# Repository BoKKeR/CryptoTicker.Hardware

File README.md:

# Work in progress

# CryptoTicker.Hardware
CryptoTicker is an information display board that supports over 1500 coin pairs. The PCB consists of 4 individual 1.3" OLED displays controlled by an ESP32. These displays can show a coin pair each. The display outputs are shifted using a multiplexor. Updating or changing the information on the fly is possible from the localhost web server that is running on the device. Vertical and Horizontal positioning is possible. There are 4 programable push-buttons located on the back of the device.
The device can be extendable to support up to 8 displays or with extra multiplexors up to 64 displays.
# Is [coin] supported?
The full list of supported coins can be found at https://coinmarketcap.com/all/views/all/
# Where is the software?
The software is available on the second repository: https://github.com/BoKKeR/CryptoTicker.Software/
# What is missing
There will be an additional board that will be powering the CryptoTicker PCB and serving as the USB to serial converter for the EPS32. There are smaller problems with this design. The files will be updated soon.
# Schematics

# PCB Design

# BOM
Incoming

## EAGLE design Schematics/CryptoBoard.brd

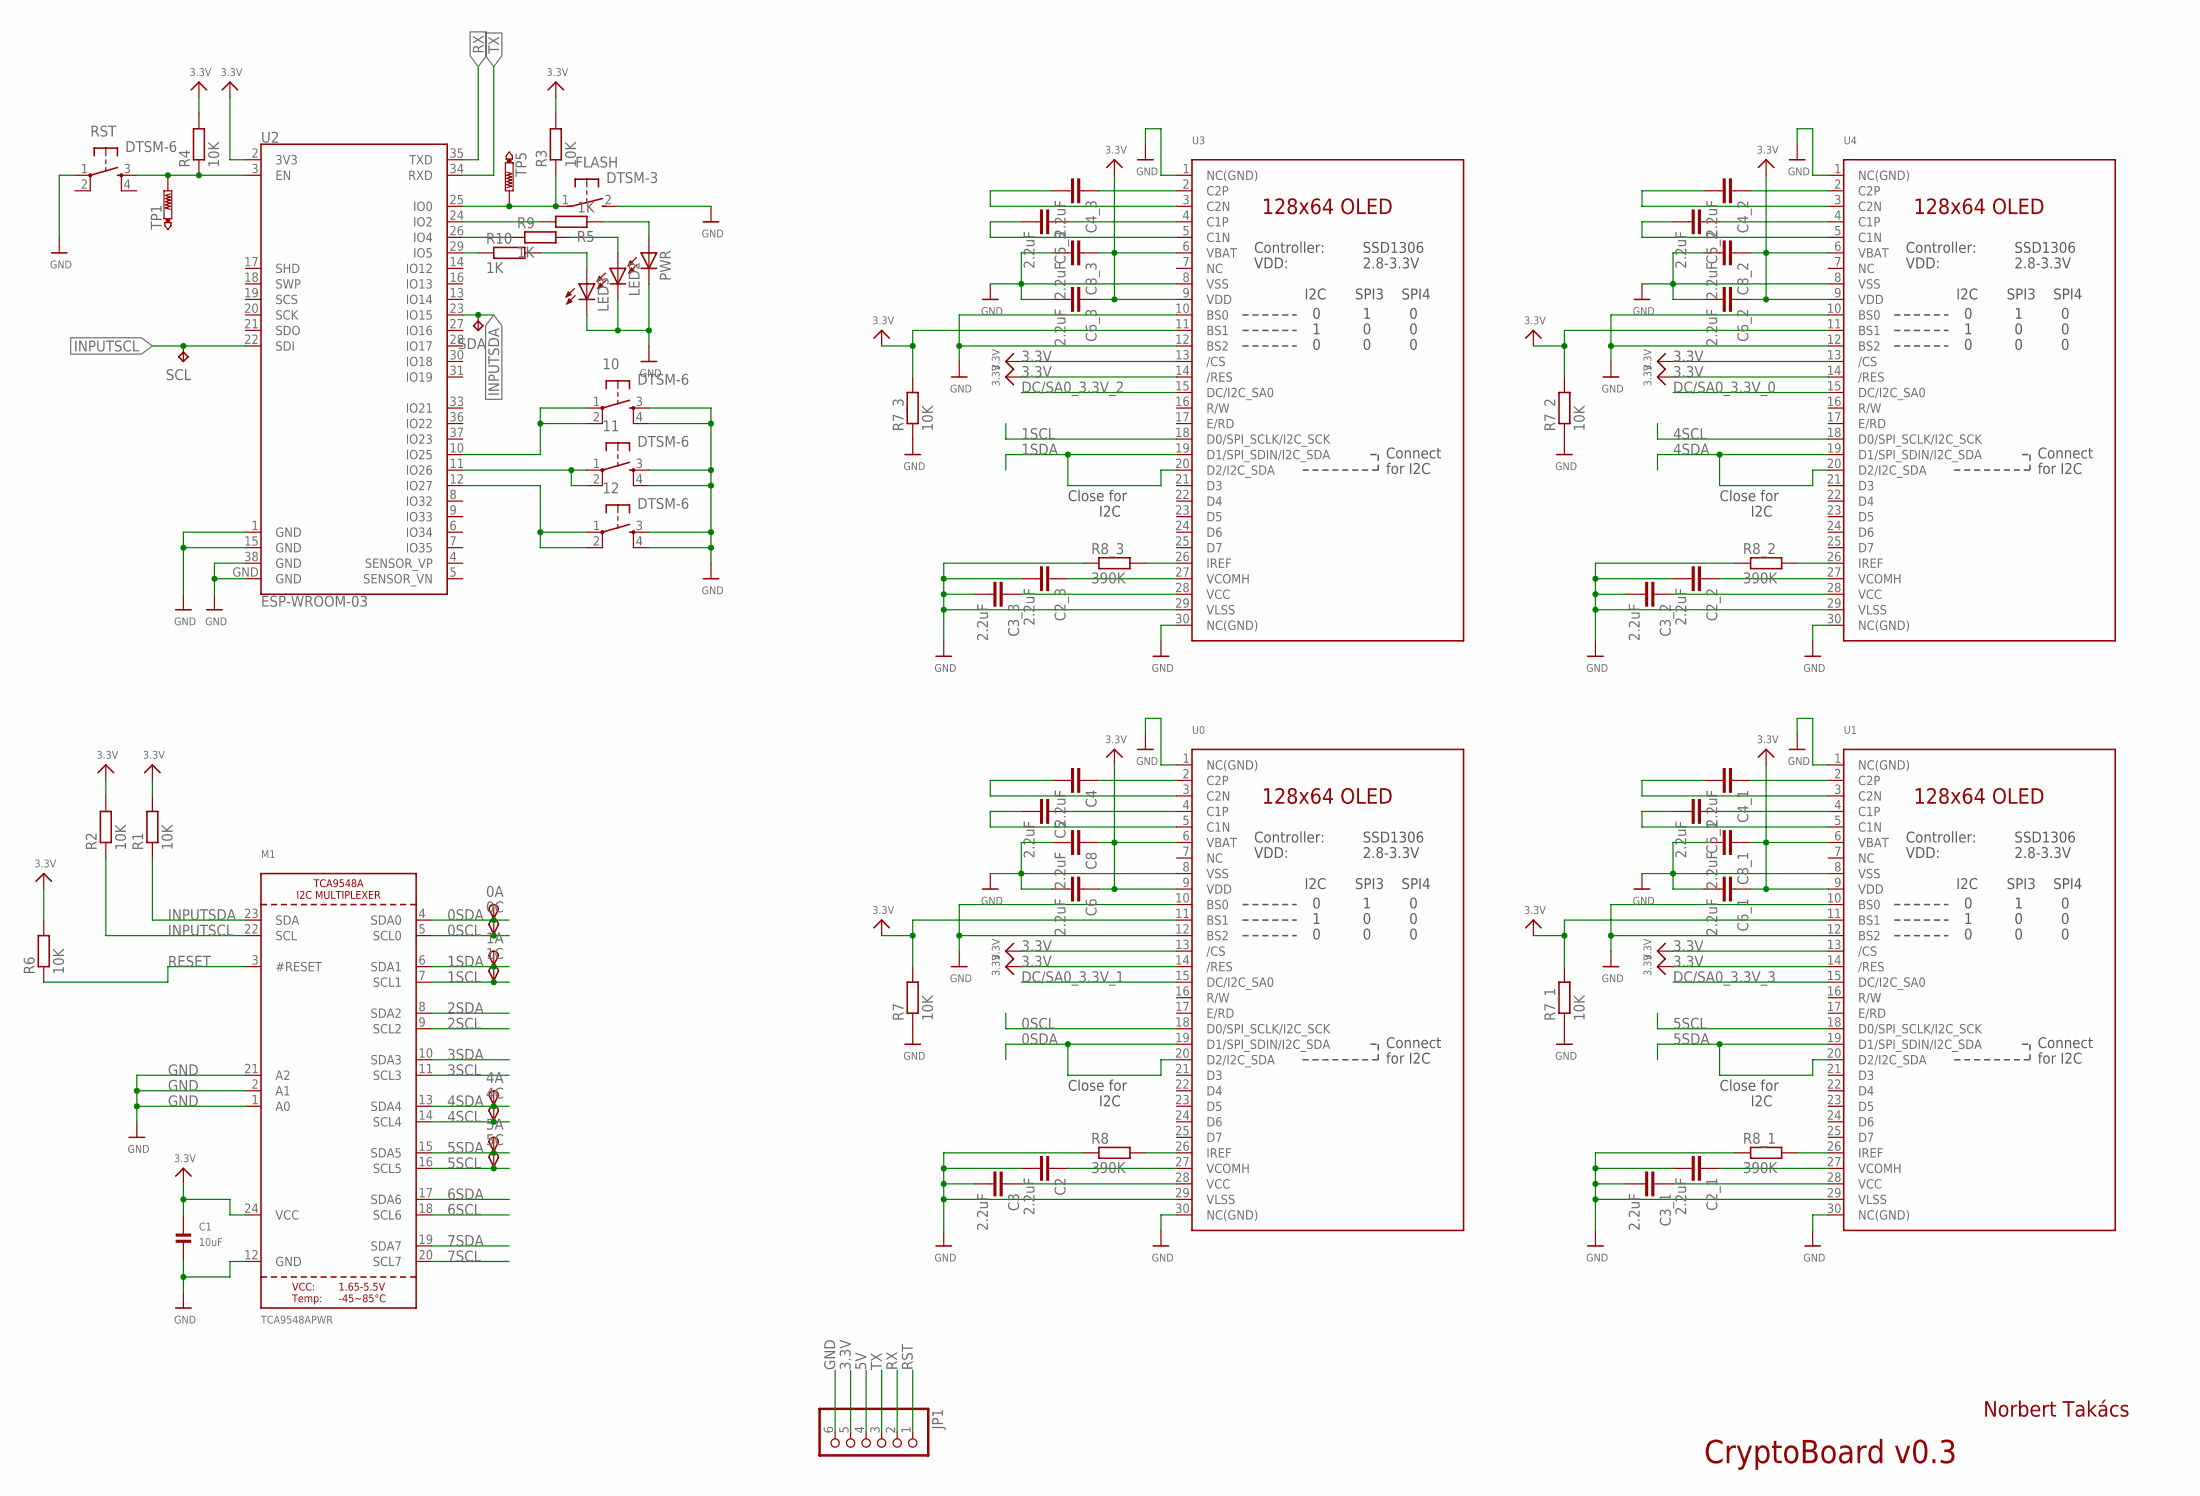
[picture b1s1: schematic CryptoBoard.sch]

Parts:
0A, 0C, 1A, 1C, 4A, 4C, 5A, 5C: TPSTP20R; TP20R
10, 11, 12: DTSM-6
C1: 10uF; 0805
C2, C2_1, C2_2, C2_3, C3, C3_1, C3_2, C3_3, C4, C4_1, C4_2, C4_3, C5, C5_1, C5_2, C5_3, C6, C6_1, C6_2, C6_3, C8, C8_1, C8_2, C8_3: 2.2uF; C0805
FLASH: DTSM-3
JP1: PINHD-1X6; 1X06
LED2, LED3: LEDSML0805; SML0805
M1: TCA9548APWR; TSSOP24
PWR: LEDSML0805; SML0805
R1, R2, R3, R4, R6, R7, R7_1, R7_2, R7_3: 10K; M0805
R5, R9, R10: 1K; M0805
R8, R8_1, R8_2, R8_3: 390K; M0805
RST: DTSM-6
SCL: TPPAD1-13; P1-13
SDA: TPPAD1-13; P1-13
TP1, TP5: PTR1B2,54; B2,54
U0, U1, U3, U4: DISP_OLED_UG-2864HSWEG01; UG-2864HSWEG01_1.3_WRAPAROUND
U2: ESP-WROOM-03

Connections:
0SCL: 0C.TP, M1.5 (SCL0), U0.18 (D0/SPI_SCLK/I2C_SCK)
0SDA: 0A.TP, M1.4 (SDA0), U0.19 (D1/SPI_SDIN/I2C_SDA), U0.20 (D2/I2C_SDA)
1SCL: 1C.TP, M1.7 (SCL1), U3.18 (D0/SPI_SCLK/I2C_SCK)
1SDA: 1A.TP, M1.6 (SDA1), U3.19 (D1/SPI_SDIN/I2C_SDA), U3.20 (D2/I2C_SDA)
2SCL: M1.9 (SCL2)
2SDA: M1.8 (SDA2)
3.3V: C1.1, C6.1, C6_1.1, C6_2.1, C6_3.1, C8.1, C8_1.1, C8_2.1, C8_3.1, JP1.5, M1.24 (VCC), R1.2, R2.2, R3.2, R4.2, R6.2, R7.2, R7_1.2, R7_2.2, R7_3.2, U0.6 (VBAT), U0.9 (VDD), U0.11 (BS1), U0.13 (/CS), U0.14 (/RES), U1.6 (VBAT), U1.9 (VDD), U1.11 (BS1), U1.13 (/CS), U1.14 (/RES), U2.2 (3V3), U3.6 (VBAT), U3.9 (VDD), U3.11 (BS1), U3.13 (/CS), U3.14 (/RES), U4.6 (VBAT), U4.9 (VDD), U4.11 (BS1), U4.13 (/CS), U4.14 (/RES)
3SCL: M1.11 (SCL3)
3SDA: M1.10 (SDA3)
4SCL: 4C.TP, M1.14 (SCL4), U4.18 (D0/SPI_SCLK/I2C_SCK)
4SDA: 4A.TP, M1.13 (SDA4), U4.19 (D1/SPI_SDIN/I2C_SDA), U4.20 (D2/I2C_SDA)
5SCL: 5C.TP, M1.16 (SCL5), U1.18 (D0/SPI_SCLK/I2C_SCK)
5SDA: 5A.TP, M1.15 (SDA5), U1.19 (D1/SPI_SDIN/I2C_SDA), U1.20 (D2/I2C_SDA)
5V: JP1.4
6SCL: M1.18 (SCL6)
6SDA: M1.17 (SDA6)
7SCL: M1.20 (SCL7)
7SDA: M1.19 (SDA7)
DC/SA0_3.3V_0: U4.15 (DC/I2C_SA0)
DC/SA0_3.3V_1: U0.15 (DC/I2C_SA0)
DC/SA0_3.3V_2: U3.15 (DC/I2C_SA0)
DC/SA0_3.3V_3: U1.15 (DC/I2C_SA0)
GND: 10.3, 10.4, 11.3, 11.4, 12.3, 12.4, C1.2, C2.2, C2_1.2, C2_2.2, C2_3.2, C3.2, C3_1.2, C3_2.2, C3_3.2, C6.2, C6_1.2, C6_2.2, C6_3.2, C8.2, C8_1.2, C8_2.2, C8_3.2, FLASH.2, JP1.6, LED2.C, LED3.C, M1.1 (A0), M1.2 (A1), M1.12 (GND), M1.21 (A2), PWR.C, R7.1, R7_1.1, R7_2.1, R7_3.1, R8.1, R8_1.1, R8_2.1, R8_3.1, RST.1, U0.1 (NC(GND)), U0.8 (VSS), U0.10 (BS0), U0.12 (BS2), U0.29 (VLSS), U0.30 (NC(GND)), U1.1 (NC(GND)), U1.8 (VSS), U1.10 (BS0), U1.12 (BS2), U1.29 (VLSS), U1.30 (NC(GND)), U2.1 (GND), U2.15 (GND), U2.38 (GND), U2.GND, U3.1 (NC(GND)), U3.8 (VSS), U3.10 (BS0), U3.12 (BS2), U3.29 (VLSS), U3.30 (NC(GND)), U4.1 (NC(GND)), U4.8 (VSS), U4.10 (BS0), U4.12 (BS2), U4.29 (VLSS), U4.30 (NC(GND))
INPUTSCL: M1.22 (SCL), R2.1, SCL.TP, U2.22 (SDI)
INPUTSDA: M1.23 (SDA), R1.1, SDA.TP, U2.23 (IO15)
unnamed: 10.1, 10.2, U2.10 (IO25)
unnamed: R8.2, U0.26 (IREF)
unnamed: C4.1, U0.2 (C2P)
unnamed: C4.2, U0.3 (C2N)
unnamed: C5.1, U0.4 (C1P)
unnamed: C5.2, U0.5 (C1N)
unnamed: R8_3.2, U3.26 (IREF)
unnamed: C3.1, U0.28 (VCC)
unnamed: C2.1, U0.27 (VCOMH)
unnamed: C4_3.1, U3.2 (C2P)
unnamed: C4_3.2, U3.3 (C2N)
unnamed: C5_3.1, U3.4 (C1P)
unnamed: C5_3.2, U3.5 (C1N)
unnamed: C3_3.1, U3.28 (VCC)
unnamed: C2_3.1, U3.27 (VCOMH)
unnamed: R8_1.2, U1.26 (IREF)
unnamed: C4_1.1, U1.2 (C2P)
unnamed: C4_1.2, U1.3 (C2N)
unnamed: C5_1.1, U1.4 (C1P)
unnamed: C5_1.2, U1.5 (C1N)
unnamed: R8_2.2, U4.26 (IREF)
unnamed: C4_2.1, U4.2 (C2P)
unnamed: C4_2.2, U4.3 (C2N)
unnamed: C5_2.1, U4.4 (C1P)
unnamed: C5_2.2, U4.5 (C1N)
unnamed: C3_2.1, U4.28 (VCC)
unnamed: C2_2.1, U4.27 (VCOMH)
unnamed: C3_1.1, U1.28 (VCC)
unnamed: C2_1.1, U1.27 (VCOMH)
unnamed: PWR.A, R5.1
unnamed: R9.1, U2.26 (IO4)
unnamed: FLASH.1, R3.1, TP5.TP, U2.25 (IO0)
unnamed: R5.2, U2.24 (IO2)
unnamed: 11.1, 11.2, U2.11 (IO26)
unnamed: 12.1, 12.2, U2.12 (IO27)
unnamed: LED2.A, R9.2
unnamed: LED3.A, R10.2
unnamed: R10.1, U2.29 (IO5)
RESET: M1.3 (#RESET), R6.1
RST: JP1.1
RX: JP1.2, U2.35 (TXD)
SHORT: R4.1, RST.3, TP1.TP, U2.3 (EN)
TX: JP1.3, U2.34 (RXD)

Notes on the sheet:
Close for
I2C
Norbert Takács
CryptoBoard v0.3

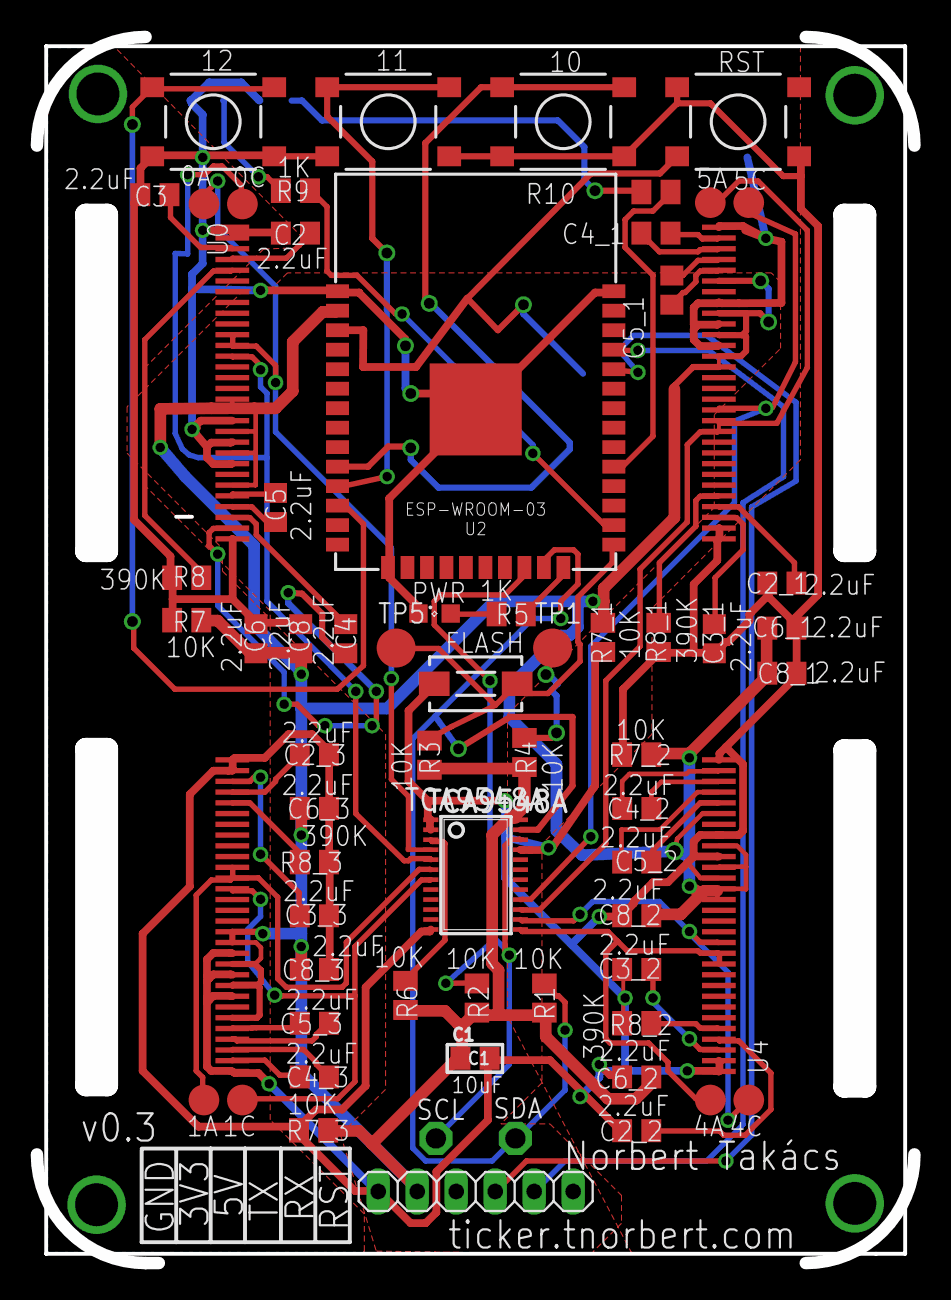
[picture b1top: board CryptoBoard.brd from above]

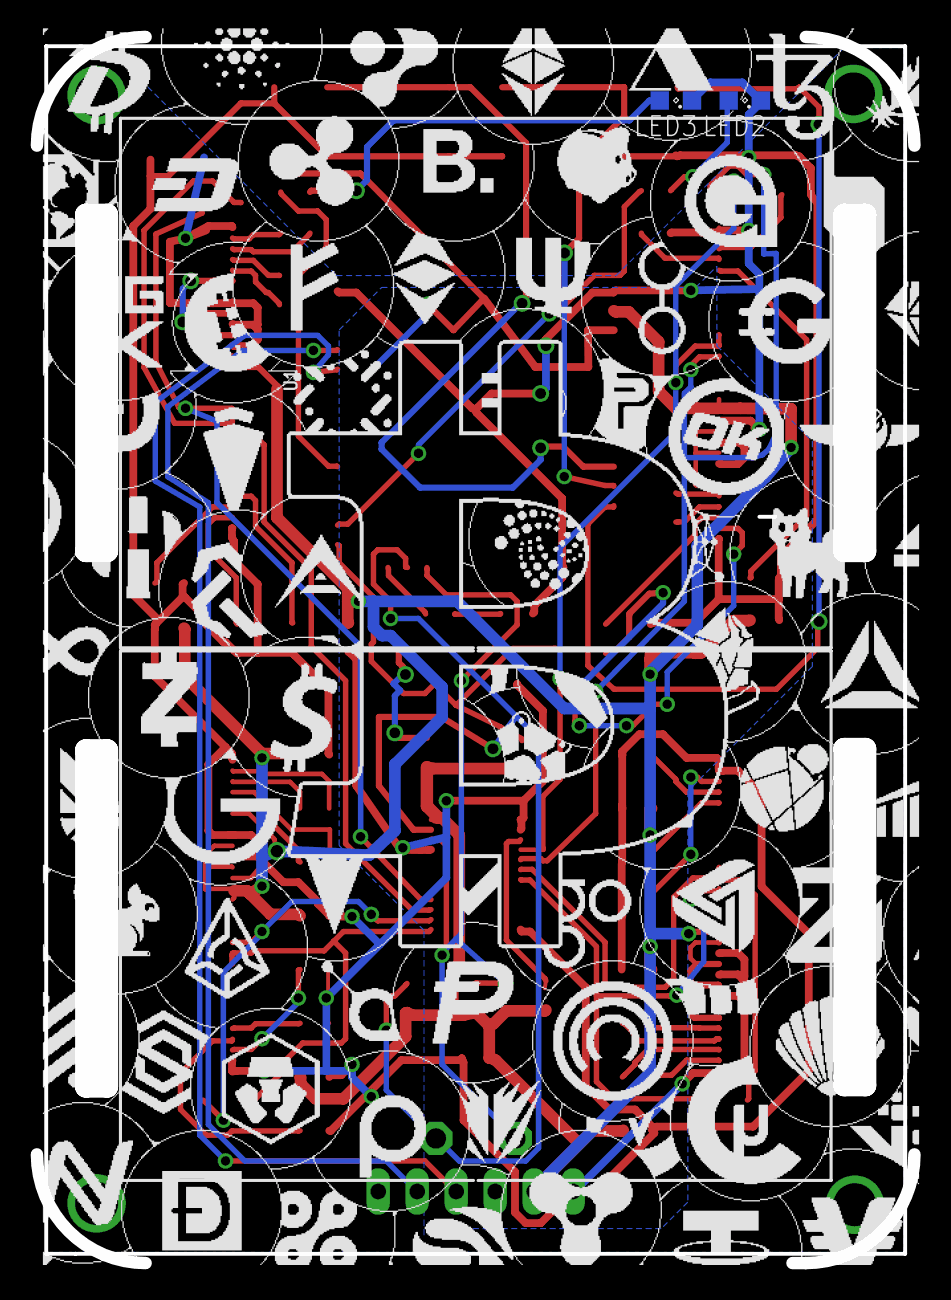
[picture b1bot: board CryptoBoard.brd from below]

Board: 2 copper layers, 56.6 x 79.3 mm, 68 parts (6 on the bottom side), 54 nets.

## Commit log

2018-05-08 First commit
    Basic readme information added.
2018-05-08 Added the link to the software repository
2018-05-08 Added schematics and board layout
2018-05-08 Fixed typos

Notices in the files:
parts and their libraries:
microbuilder: This work is placed in the public domain, and may be freely used for commercial and non-commercial work with the following conditions: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
